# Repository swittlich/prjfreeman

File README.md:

# prjfreeman: the Xilinx XC2064 in yosys and nextpnr

The XC2064 (1985) was the first FPGA: 64 Configurable Logic Blocks (CLBs) in an 8×8 grid and 58 I/O pins.
This repo models it as a nextpnr Himbächel uarch with a yosys plugin, so that Verilog designs can be
synthesized, placed and routed for the original chip and turned into a bitstream in the format of Xilinx's
XACT, all with an open-source flow.

> [!WARNING]
> **Not tested on real hardware.** None of the generated bitstreams has been loaded onto a real XC2064 yet.
> For 44 test runs, MAKEBITS from Xilinx's XACT produces bit-identical bitstreams from the same placement and
> routing, but the clock buffer codes come from XACT's model, and the edge of the IOB flip-flop and Shirriff's
> K mux codes have not been checked on a chip. See [Open items](docs/development-stages.md#open-items).

## What it can do

- **Synthesis:** the yosys plugin `synth_xc2064` maps Verilog onto the function generators of the CLBs (3- and
  4-input LUTs, the FGM mux mode), flip-flops and latches with asynchronous set/reset, latched inputs in the
  IOB and tristate or bidirectional pads.
- **Place & route:** a routing graph built from the real configuration bits (switch matrices, PIPs,
  single-length segments, Long Lines, the clock buffers GCLK and ACLK, repowering buffers), an exact legality
  check of every CLB, and timing for the speed grades -50 to -130 from the Xilinx Data Books.
- **Packages:** PC68, PD48, PC44 and PG68, pins constrained with a PCF file.
- **GUI:** a schematic of the whole chip with all lines, Bels and pips, in which every routed path can be
  followed from the pad to the flip-flop.
- **Bitstream:** `xc2064pack` writes RBT and BIT files in XACT's format; `xc2064unpack` and `xc2064netlist`
  turn a bitstream back into readable text and into a netlist.
- **Verification:** a regression test proves every result formally equivalent to the RTL (after routing, from
  the used pips alone and from the bitstream) and cross-checks the bitstreams with Ken Shirriff's independent
  decoder and with XACT.

## Quick start

This repo lives as `arch/xc2064` in the repo that builds yosys and nextpnr (`scripts/build-nextpnr.sh`); the
commands run from that repo's root:

```bash
git clone --recurse-submodules https://github.com/swittlich/prjfreeman arch/xc2064
scripts/build-nextpnr.sh debug     # nextpnr with the xc2064 uarch
arch/xc2064/flow.sh --gui          # synthesize examples/blinky.v, then Pack, Place, Route in the GUI
arch/xc2064/test/run.sh            # regression test over all examples
```

## Documentation

| Document | Contents |
|---|---|
| [Getting started](docs/getting-started.md) | Setup, running the flow, packages and speed grades, VS Code |
| [Examples](docs/examples.md) | The example designs and their results |
| [Architecture model](docs/architecture.md) | What is modelled and how: routing, CLBs, IOBs, clocks, packages, timing |
| [Synthesis](docs/yosys.md) | The yosys plugin `synth_xc2064` and its passes |
| [nextpnr uarch](docs/nextpnr.md) | Legality checks, packing, primitives, pin constraints, routing |
| [GUI](docs/gui.md) | How the chip is drawn |
| [Bitstream](docs/bitstream.md) | Generating bitstreams, the bitstream and text formats, the tools |
| [Testing](docs/testing.md) | Regression test, formal comparison, cross-check with Shirriff's decoder |
| [Data sources](docs/data-sources.md) | References, submodules, the `xc2064db` package, what the data tell us about the original |
| [Cross-checks with XACT](docs/xact.md) | Clock buffer codes from MAKEBITS, XNF netlists for XNFMAP |
| [Development stages](docs/development-stages.md) | Open items and how the model was built |

## Contributing

Contributions are welcome: bug reports, questions, improvements to the model, the tools or the documentation,
and above all anyone who can try a bitstream on a real XC2064. Please open an issue or a pull request on
[GitHub](https://github.com/swittlich/prjfreeman). Before submitting changes to the model or the tools, run
`arch/xc2064/test/run.sh` (every run must pass) and, for the bitstream tools, `arch/xc2064/test/bitstreams.sh`.
Contributions are accepted under the same license as the project (ISC, see [License](#license)).

## Acknowledgements

This work builds on Ken Shirriff's reverse engineering of the XC2064
([blog post](https://www.righto.com/2020/09/reverse-engineering-first-fpga-chip.html),
[shirriff/xc2064](https://github.com/shirriff/xc2064)), the XACT bitstreams in
[rates37/openxc2064](https://github.com/rates37/openxc2064) and the Xilinx Data Books. All references are
listed in [Data sources](docs/data-sources.md#references).

## License

Copyright (C) 2026 Sebastian Wittlich

This project is licensed under the [ISC License](LICENSE), the same permissive license as yosys and
nextpnr. In short: you may use, copy, change and distribute it, also commercially and as part of closed
source, as long as the copyright notice and the permission notice are kept. It comes without any warranty.

The submodules in `external/` keep their own licenses. Your own designs and the netlists and bitstreams the
tools generate from them are not affected by the license of this project.

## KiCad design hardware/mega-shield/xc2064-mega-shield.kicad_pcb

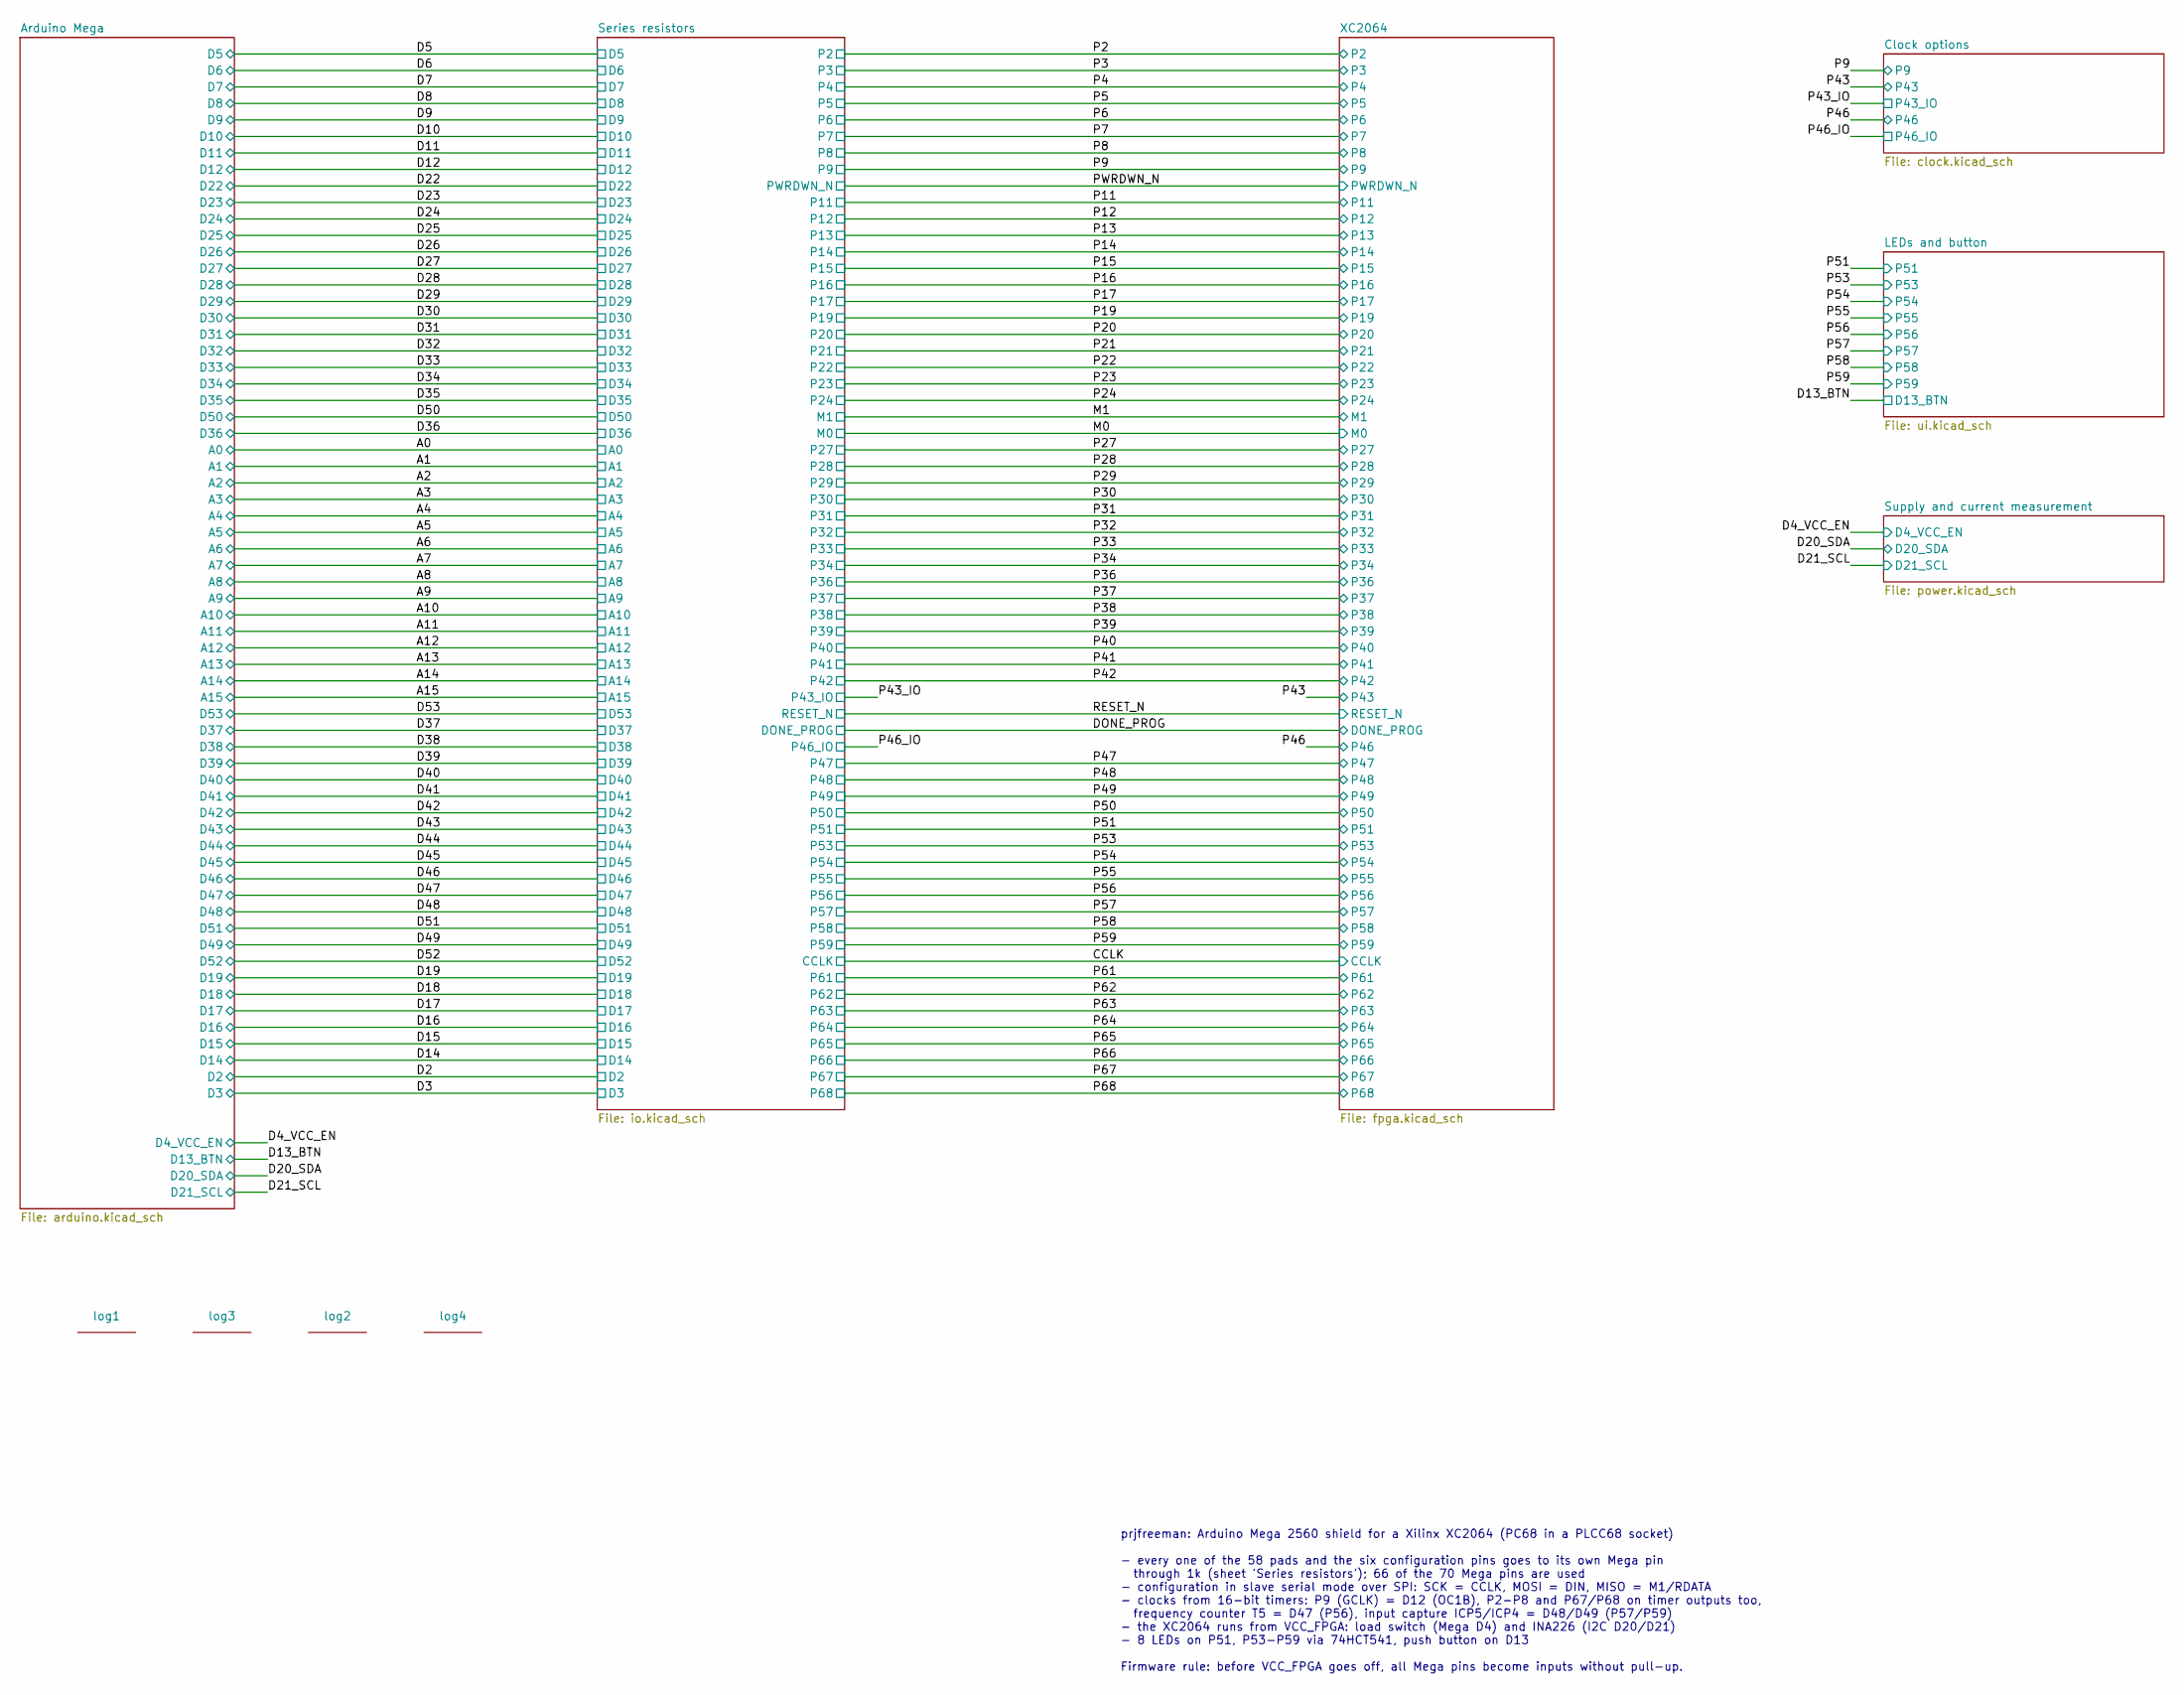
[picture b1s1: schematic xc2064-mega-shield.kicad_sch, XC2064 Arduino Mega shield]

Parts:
log1: OpenHardwareLogo
log2: QR_prjfreeman
log3: RobotLogo
log4: TH_Koeln_Logo

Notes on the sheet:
prjfreeman: Arduino Mega 2560 shield for a Xilinx XC2064 (PC68 in a PLCC68 socket) - every one of the 58 pads and the six configuration pins goes to its own Mega pin through 1k (sheet 'Series resistors'); 66 of the 70 Mega pins are used - configuration in slave serial mode over SPI: SCK = CCLK, MOS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

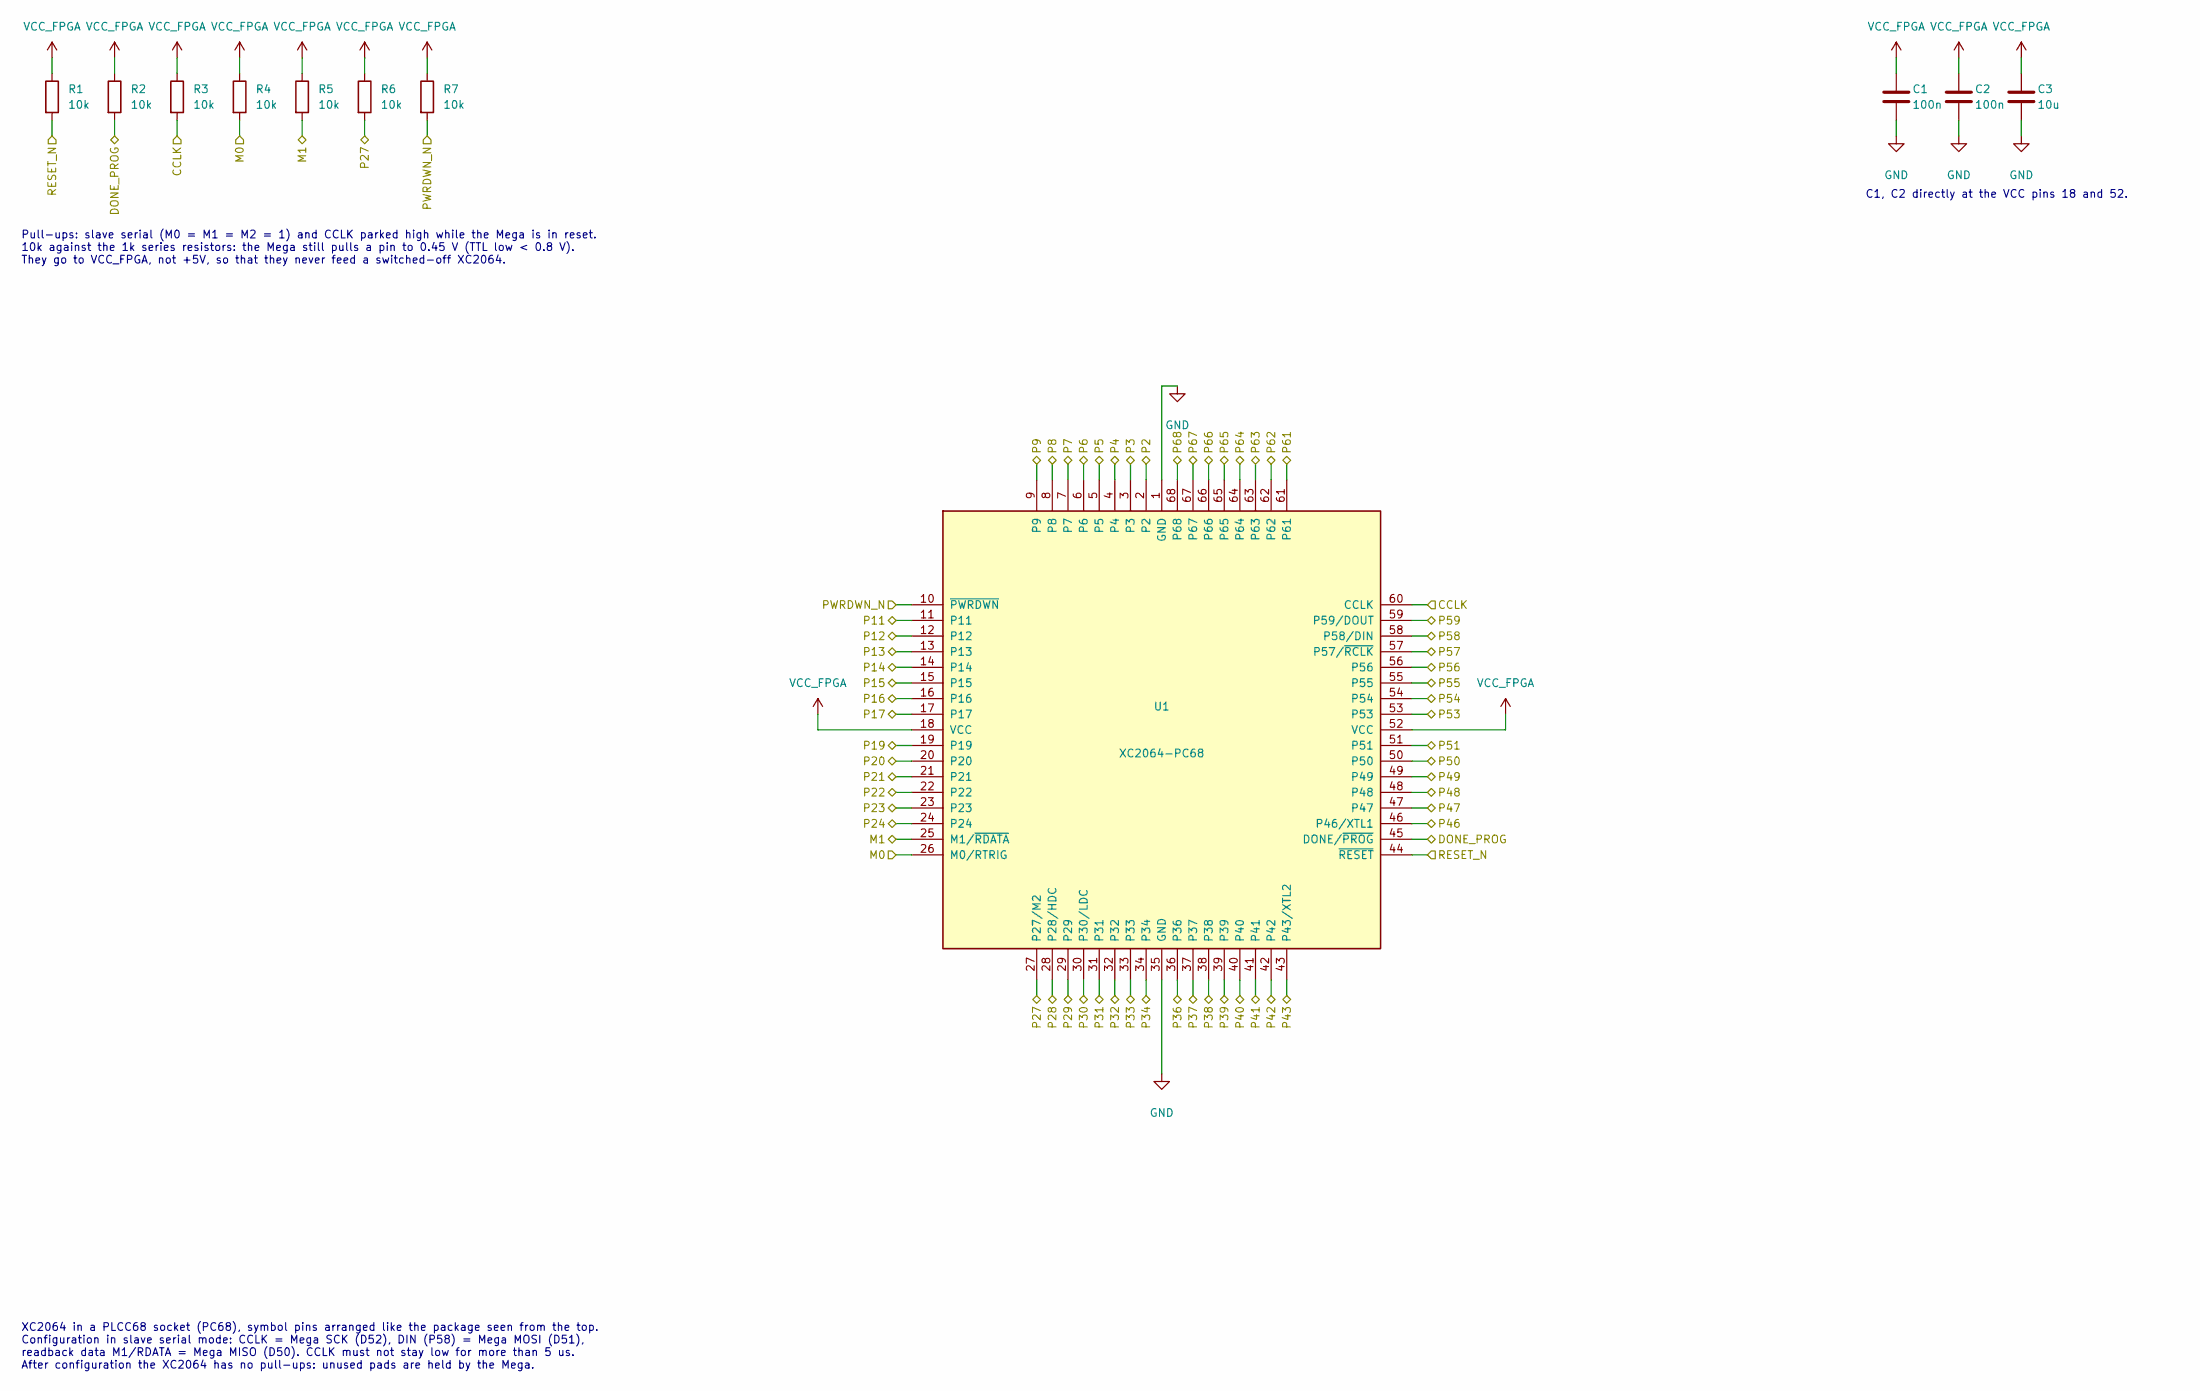
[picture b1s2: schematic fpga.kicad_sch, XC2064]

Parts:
C1, C2: 100n; C_0805_2012Metric; MPN CC0805KRX7R9BB104; LCSC C49678
C3: 10u; C_1206_3216Metric; MPN CL31A106KBHNNNE; LCSC C13585
R1, R2, R3, R4, R5, R6, R7: 10k; R_0805_2012Metric; MPN 0805W8F1002T5E; LCSC C17414
U1: XC2064-PC68; PLCC-68_THT-Socket; MPN PLCC-68-AT; LCSC C6735534

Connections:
/CCLK: R3.2, U1.60 (CCLK); also elsewhere on the board
/DONE_PROG: R2.2, U1.45 (DONE/~PROG); also elsewhere on the board
/M0: R4.2, U1.26 (M0/RTRIG); also elsewhere on the board
/M1: R5.2, U1.25 (M1/~RDATA); also elsewhere on the board
/P2: U1.2; also elsewhere on the board
/P3: U1.3; also elsewhere on the board
/P4: U1.4; also elsewhere on the board
/P5: U1.5; also elsewhere on the board
/P6: U1.6; also elsewhere on the board
/P7: U1.7; also elsewhere on the board
/P8: U1.8; also elsewhere on the board
/P9: U1.9; also elsewhere on the board
/P11: U1.11; also elsewhere on the board
/P12: U1.12; also elsewhere on the board
/P13: U1.13; also elsewhere on the board
/P14: U1.14; also elsewhere on the board
/P15: U1.15; also elsewhere on the board
/P16: U1.16; also elsewhere on the board
/P17: U1.17; also elsewhere on the board
/P19: U1.19; also elsewhere on the board
/P20: U1.20; also elsewhere on the board
/P21: U1.21; also elsewhere on the board
/P22: U1.22; also elsewhere on the board
/P23: U1.23; also elsewhere on the board
/P24: U1.24; also elsewhere on the board
/P27: R6.2, U1.27 (P27/M2); also elsewhere on the board
/P28: U1.28 (P28/HDC); also elsewhere on the board
/P29: U1.29; also elsewhere on the board
/P30: U1.30 (P30/LDC); also elsewhere on the board
/P31: U1.31; also elsewhere on the board
/P32: U1.32; also elsewhere on the board
/P33: U1.33; also elsewhere on the board
/P34: U1.34; also elsewhere on the board
/P36: U1.36; also elsewhere on the board
/P37: U1.37; also elsewhere on the board
/P38: U1.38; also elsewhere on the board
/P39: U1.39; also elsewhere on the board
/P40: U1.40; also elsewhere on the board
/P41: U1.41; also elsewhere on the board
/P42: U1.42; also elsewhere on the board
/P43: U1.43 (P43/XTL2); also elsewhere on the board
/P46: U1.46 (P46/XTL1); also elsewhere on the board
/P47: U1.47; also elsewhere on the board
/P48: U1.48; also elsewhere on the board
/P49: U1.49; also elsewhere on the board
/P50: U1.50; also elsewhere on the board
/P51: U1.51; also elsewhere on the board
/P53: U1.53; also elsewhere on the board
/P54: U1.54; also elsewhere on the board
/P55: U1.55; also elsewhere on the board
/P56: U1.56; also elsewhere on the board
/P57: U1.57 (P57/~RCLK); also elsewhere on the board
/P58: U1.58 (P58/DIN); also elsewhere on the board
/P59: U1.59 (P59/DOUT); also elsewhere on the board
/P61: U1.61; also elsewhere on the board
/P62: U1.62; also elsewhere on the board
/P63: U1.63; also elsewhere on the board
/P64: U1.64; also elsewhere on the board
/P65: U1.65; also elsewhere on the board
/P66: U1.66; also elsewhere on the board
/P67: U1.67; also elsewhere on the board
/P68: U1.68; also elsewhere on the board
/PWRDWN_N: R7.2, U1.10 (~PWRDWN); also elsewhere on the board
/RESET_N: R1.2, U1.44 (~RESET); also elsewhere on the board
GND: C1.2, C2.2, C3.2, U1.1 (GND), U1.35 (GND); also elsewhere on the board
VCC_FPGA: C1.1, C2.1, C3.1, R1.1, R2.1, R3.1, R4.1, R5.1, R6.1, R7.1, U1.18 (VCC), U1.52 (VCC); also elsewhere on the board

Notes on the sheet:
Pull-ups: slave serial (M0 = M1 = M2 = 1) and CCLK parked high while the Mega is in reset. 10k against the 1k series resistors: the Mega still pulls a pin to 0.45 V (TTL low < 0.8 V). They go to VCC_FPGA, not +5V, so that they never feed a switched-off XC2064.
C1, C2 directly at the VCC pins 18 and 52.
XC2064 in a PLCC68 socket (PC68), symbol pins arranged like the package seen from the top. Configuration in slave serial mode: CCLK = Mega SCK (D52), DIN (P58) = Mega MOSI (D51), readback data M1/RDATA = Mega MISO (D50). CCLK must not stay low for more than 5 us. After configuration the XC2064 has 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

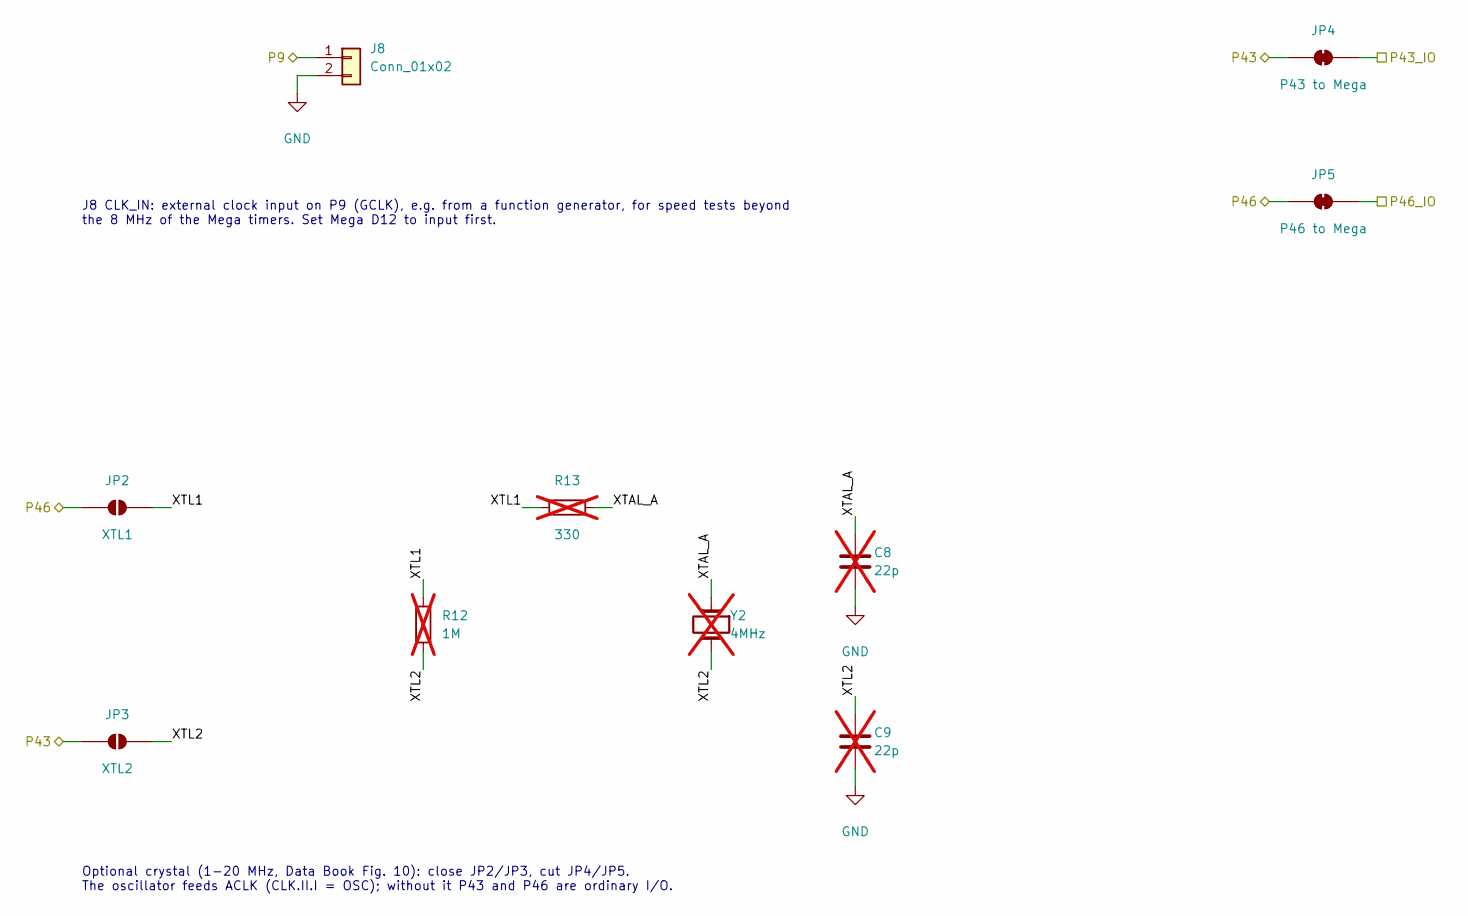
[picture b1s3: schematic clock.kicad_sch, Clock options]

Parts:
C8, C9: 22p; C_0805_2012Metric; MPN CL21C220JBANNNC; LCSC C1804; not fitted
J8: Conn_01x02; PinHeader_1x02_P2.54mm_Vertical; MPN PZ254V-11-02P; LCSC C492401
JP2: XTL1; SolderJumper-2_P1.3mm_Open_RoundedPad1.0x1.5mm
JP3: XTL2; SolderJumper-2_P1.3mm_Open_RoundedPad1.0x1.5mm
JP4: P43 to Mega; SolderJumper-2_P1.3mm_Bridged_RoundedPad1.0x1.5mm
JP5: P46 to Mega; SolderJumper-2_P1.3mm_Bridged_RoundedPad1.0x1.5mm
R12: 1M; R_0805_2012Metric; MPN 0805W8F1004T5E; LCSC C17514; not fitted
R13: 330; R_0805_2012Metric; MPN 0805W8F3300T5E; LCSC C17630; not fitted
Y2: 4MHz; Crystal_HC49-4H_Vertical; MPN X49SD4MSD2SC; LCSC C13761; not fitted

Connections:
/Clock options/XTAL_A: C8.1, R13.1, Y2.1
/Clock options/XTL1: JP2.2 (B), R12.1, R13.2
/Clock options/XTL2: C9.1, JP3.2 (B), R12.2, Y2.2
/P9: J8.1; also elsewhere on the board
/P43: JP3.1 (A), JP4.1 (A); also elsewhere on the board
/P43_IO: JP4.2 (B); also elsewhere on the board
/P46: JP2.1 (A), JP5.1 (A); also elsewhere on the board
/P46_IO: JP5.2 (B); also elsewhere on the board
GND: C8.2, C9.2, J8.2; also elsewhere on the board

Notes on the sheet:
Optional crystal (1-20 MHz, Data Book Fig. 10): close JP2/JP3, cut JP4/JP5. The oscillator feeds ACLK (CLK.II.I = OSC); without it P43 and P46 are ordinary I/O.
J8 CLK_IN: external clock input on P9 (GCLK), e.g. from a function generator, for speed tests beyond the 8 MHz of the Mega timers. Set Mega D12 to input first.

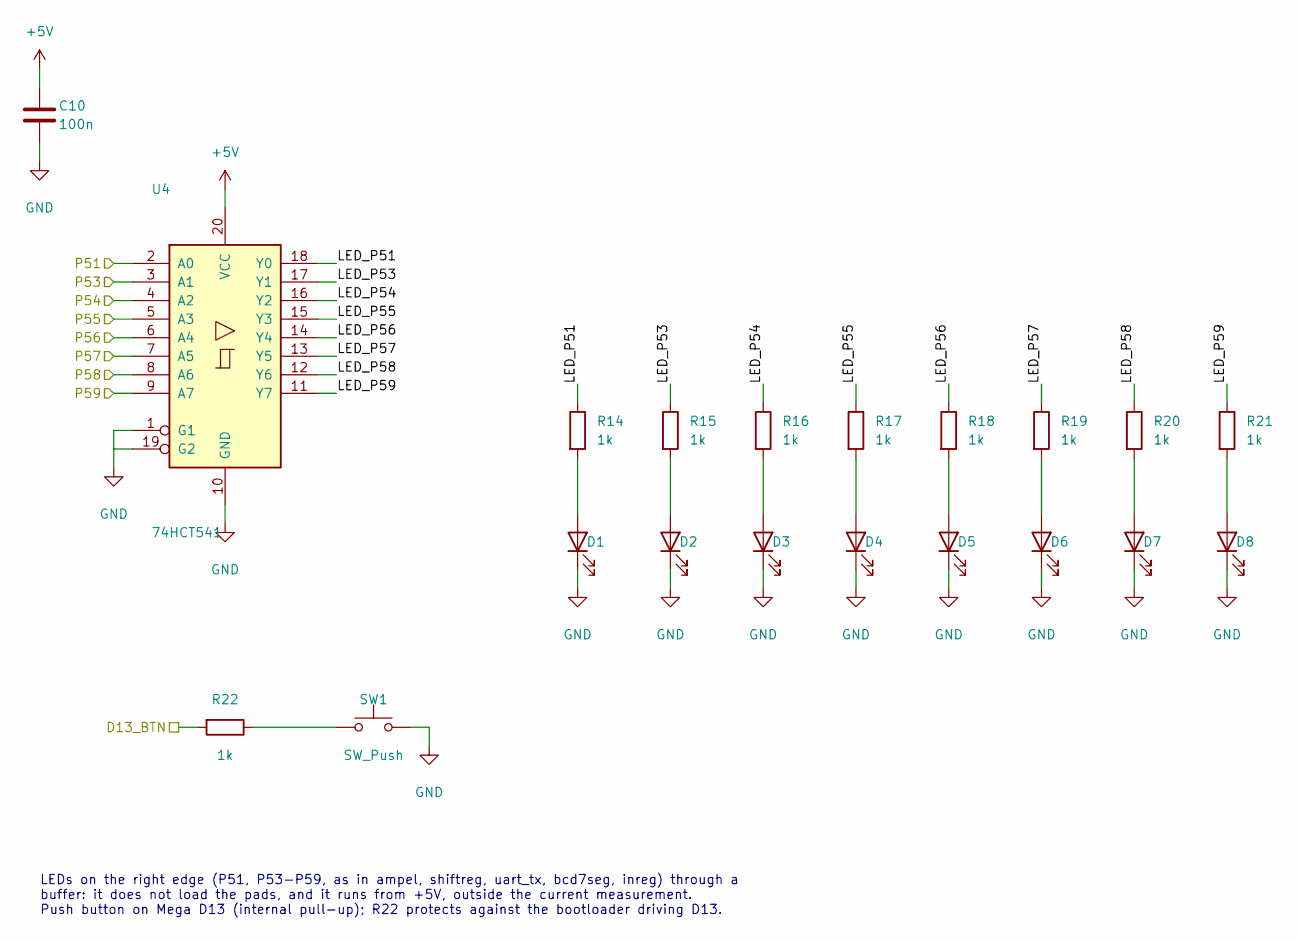
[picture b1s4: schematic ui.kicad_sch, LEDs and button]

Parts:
C10: 100n; C_0805_2012Metric; MPN CC0805KRX7R9BB104; LCSC C49678
D1, D2, D3, D4, D5, D6, D7, D8: LED; LED_0603_1608Metric; MPN KT-0603R; LCSC C2286
R14, R15, R16, R17, R18, R19, R20, R21, R22: 1k; R_0603_1608Metric; MPN 0603WAF1001T5E; LCSC C21190
SW1: SW_Push; SW_SPST_PTS645Sx43SMTR92; MPN PTS645SM43SMTR92 LFS; LCSC C221880
U4: 74HCT541; SOIC-20W_7.5x12.8mm_P1.27mm; MPN SN74HCT541DWR; LCSC C352960

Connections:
+5V: C10.1, U4.20 (VCC); also elsewhere on the board
/D13_BTN: R22.2; also elsewhere on the board
/LEDs and button/LED_P51: R14.1, U4.18 (Y0)
/LEDs and button/LED_P53: R15.1, U4.17 (Y1)
/LEDs and button/LED_P54: R16.1, U4.16 (Y2)
/LEDs and button/LED_P55: R17.1, U4.15 (Y3)
/LEDs and button/LED_P56: R18.1, U4.14 (Y4)
/LEDs and button/LED_P57: R19.1, U4.13 (Y5)
/LEDs and button/LED_P58: R20.1, U4.12 (Y6)
/LEDs and button/LED_P59: R21.1, U4.11 (Y7)
/P51: U4.2 (A0); also elsewhere on the board
/P53: U4.3 (A1); also elsewhere on the board
/P54: U4.4 (A2); also elsewhere on the board
/P55: U4.5 (A3); also elsewhere on the board
/P56: U4.6 (A4); also elsewhere on the board
/P57: U4.7 (A5); also elsewhere on the board
/P58: U4.8 (A6); also elsewhere on the board
/P59: U4.9 (A7); also elsewhere on the board
GND: C10.2, D1.1 (K), D2.1 (K), D3.1 (K), D4.1 (K), D5.1 (K), D6.1 (K), D7.1 (K), D8.1 (K), SW1.2, U4.1 (G1), U4.10 (GND), U4.19 (G2); also elsewhere on the board
unnamed: D1.2 (A), R14.2
unnamed: D2.2 (A), R15.2
unnamed: D3.2 (A), R16.2
unnamed: D4.2 (A), R17.2
unnamed: D5.2 (A), R18.2
unnamed: D6.2 (A), R19.2
unnamed: D7.2 (A), R20.2
unnamed: D8.2 (A), R21.2
unnamed: R22.1, SW1.1

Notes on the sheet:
LEDs on the right edge (P51, P53-P59, as in ampel, shiftreg, uart_tx, bcd7seg, inreg) through a buffer: it does not load the pads, and it runs from +5V, outside the current measurement. Push button on Mega D13 (internal pull-up); R22 protects against the bootloader driving D13.

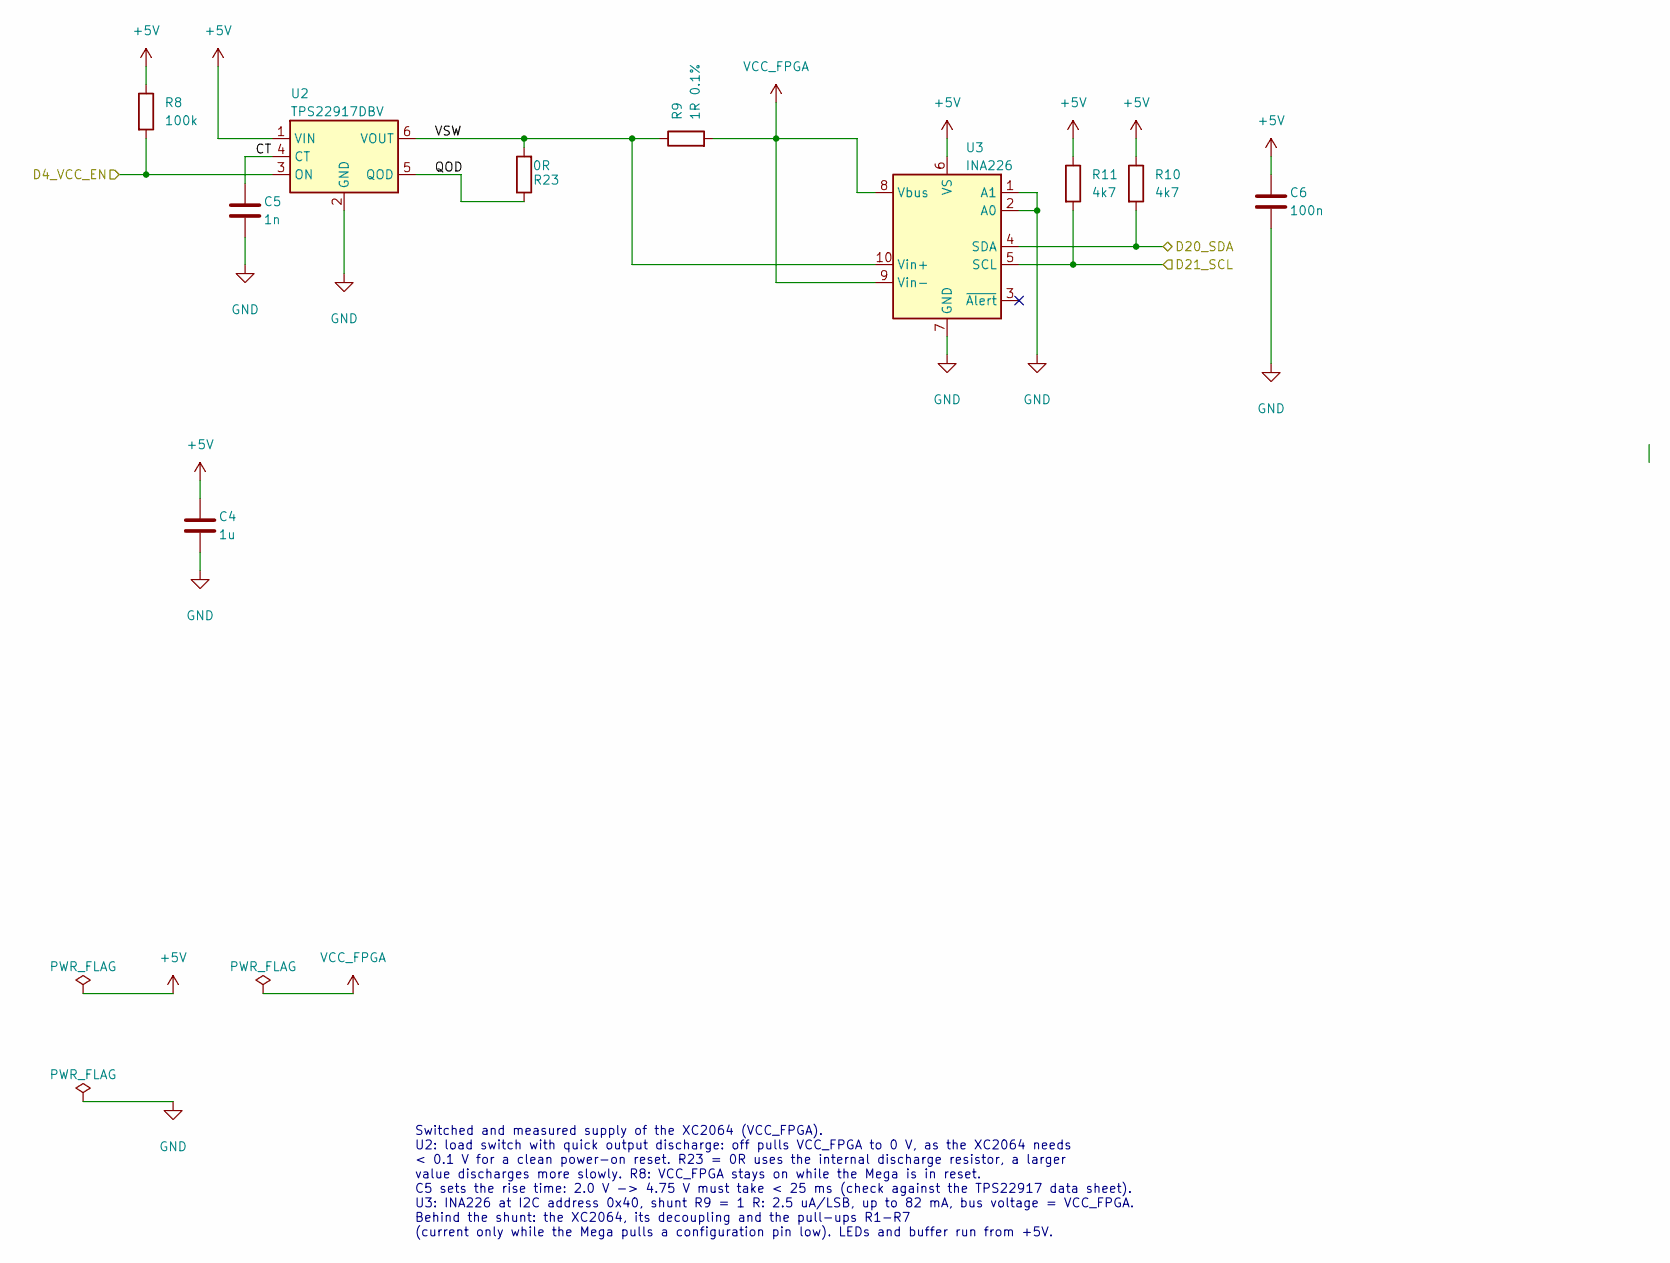
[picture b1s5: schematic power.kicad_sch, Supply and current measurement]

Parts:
C4: 1u; C_0805_2012Metric; MPN CL21B105KBFNNNE; LCSC C28323
C5: 1n; C_0805_2012Metric; MPN CL21B102KBCNNNC; LCSC C46653
C6: 100n; C_0805_2012Metric; MPN CC0805KRX7R9BB104; LCSC C49678
R8: 100k; R_0805_2012Metric; MPN 0805W8F1003T5E; LCSC C149504
R9: 1R 0.1%; R_0805_2012Metric; MPN RT0805BRD071RL; LCSC C865286
R10, R11: 4k7; R_0805_2012Metric; MPN 0805W8F4701T5E; LCSC C17673
R23: 0R; R_0603_1608Metric; MPN 0603WAF0000T5E; LCSC C21189
U2: TPS22917DBV; SOT-23-6; MPN TPS22917DBVR; LCSC C2681320
U3: INA226; TSSOP-10_3x3mm_P0.5mm; MPN INA226AIDGSR; LCSC C49851

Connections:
+5V: C4.1, C6.1, R8.1, R10.1, R11.1, U2.1 (VIN), U3.6 (VS); also elsewhere on the board
/D4_VCC_EN: R8.2, U2.3 (ON); also elsewhere on the board
/D20_SDA: R10.2, U3.4 (SDA); also elsewhere on the board
/D21_SCL: R11.2, U3.5 (SCL); also elsewhere on the board
/Supply and current measurement/CT: C5.1, U2.4 (CT)
GND: C4.2, C5.2, C6.2, U2.2 (GND), U3.1 (A1), U3.2 (A0), U3.7 (GND); also elsewhere on the board
VCC_FPGA: R9.2, U3.8 (Vbus), U3.9 (Vin-); also elsewhere on the board

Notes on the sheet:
Switched and measured supply of the XC2064 (VCC_FPGA). U2: load switch with quick output discharge: off pulls VCC_FPGA to 0 V, as the XC2064 needs < 0.1 V for a clean power-on reset. R23 = 0R uses the internal discharge resistor, a larger value discharges more slowly. R8: VCC_FPGA stays on while th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
